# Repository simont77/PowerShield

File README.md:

# PowerShield
 This design is an extension board for any Raspberry Pi based astronomy tool, like Astroberry or StellarMate.
 The repository contains the electrical (ECAD) and mechanical (MCAD) design files.
 
# Electrical Design (ECAD)

## Features
* One power input
* 4pcs switchable (ON/OFF) not regulated outpus, each has maximum 3A load capability (CH1 ... CH4 - DC jack)
* 2pcs switchable (ON/OFF) or PWM controlled outputs, also with maximum 3A load capability for dew heaters (DEW1 and DEW2 - RCA)
* Fuse monitoring signals for each outputs, to detect fuse burn
* Integrated 5V/3A SMPS to power Raspberry Pi
* Integrated BME280 to measure, temperature, pressure and humidity
* Integrated GPS module with integrated antenna
* Connecting external GPS antenna
* Fan connector, supports 3,3V and 5V fans, fan can be switched ON/OFF.
* Input voltage monitoring, maximal range 20V
* Total output current monitoring, maximal range 16A, allowed total ouput curren is 15A
* Reverse polarity protection
* 4 pin 3,5mm jack to connect external sensors, or extension boards, communication interface can be selected with jumpers, I2C or one wire
* LED feedback for each outputs
* LED for GPS, e.g. show 3D fix (usage of this LED is SW dependent)

List of used ports and their funtions will be available in the Wiki section.

## What works
 Every features listed above are tested and working. Testing was done with terminal commands, like "gpio" or with testing scripts.

## What is not working
 Check the "Issues" section.

## What is needed
* INDI driver is on the way: https://github.com/rkaczorek/astroberry-powershield
* I am planning to perform thermal measurement, to see what is board thermal behaviour under maximal load condition.

# Mechanical Design (MCAD)
 Mechanical design was done based on Hammond Extruded Aluminum Enclosures design.

 The "extruded" part of the housing is prepared for 3D printing.
 The front and back plates are design in KiCAD as well and manufactured from 1,6mm thick PCB, the panelized gerber files are uploaded in the repository.

# Licence
 The licence is the CERN Open Hardware Licence version 2, and variant CERN-OHL-S
 Check the "LICENCE" file or original location of the licence:
 https://ohwr.org/cern_ohl_s_v2.txt
 
# Donation
If you like the design, think about to support me with a cup of coffee, a glas of beer...
This could help to develop further this design.

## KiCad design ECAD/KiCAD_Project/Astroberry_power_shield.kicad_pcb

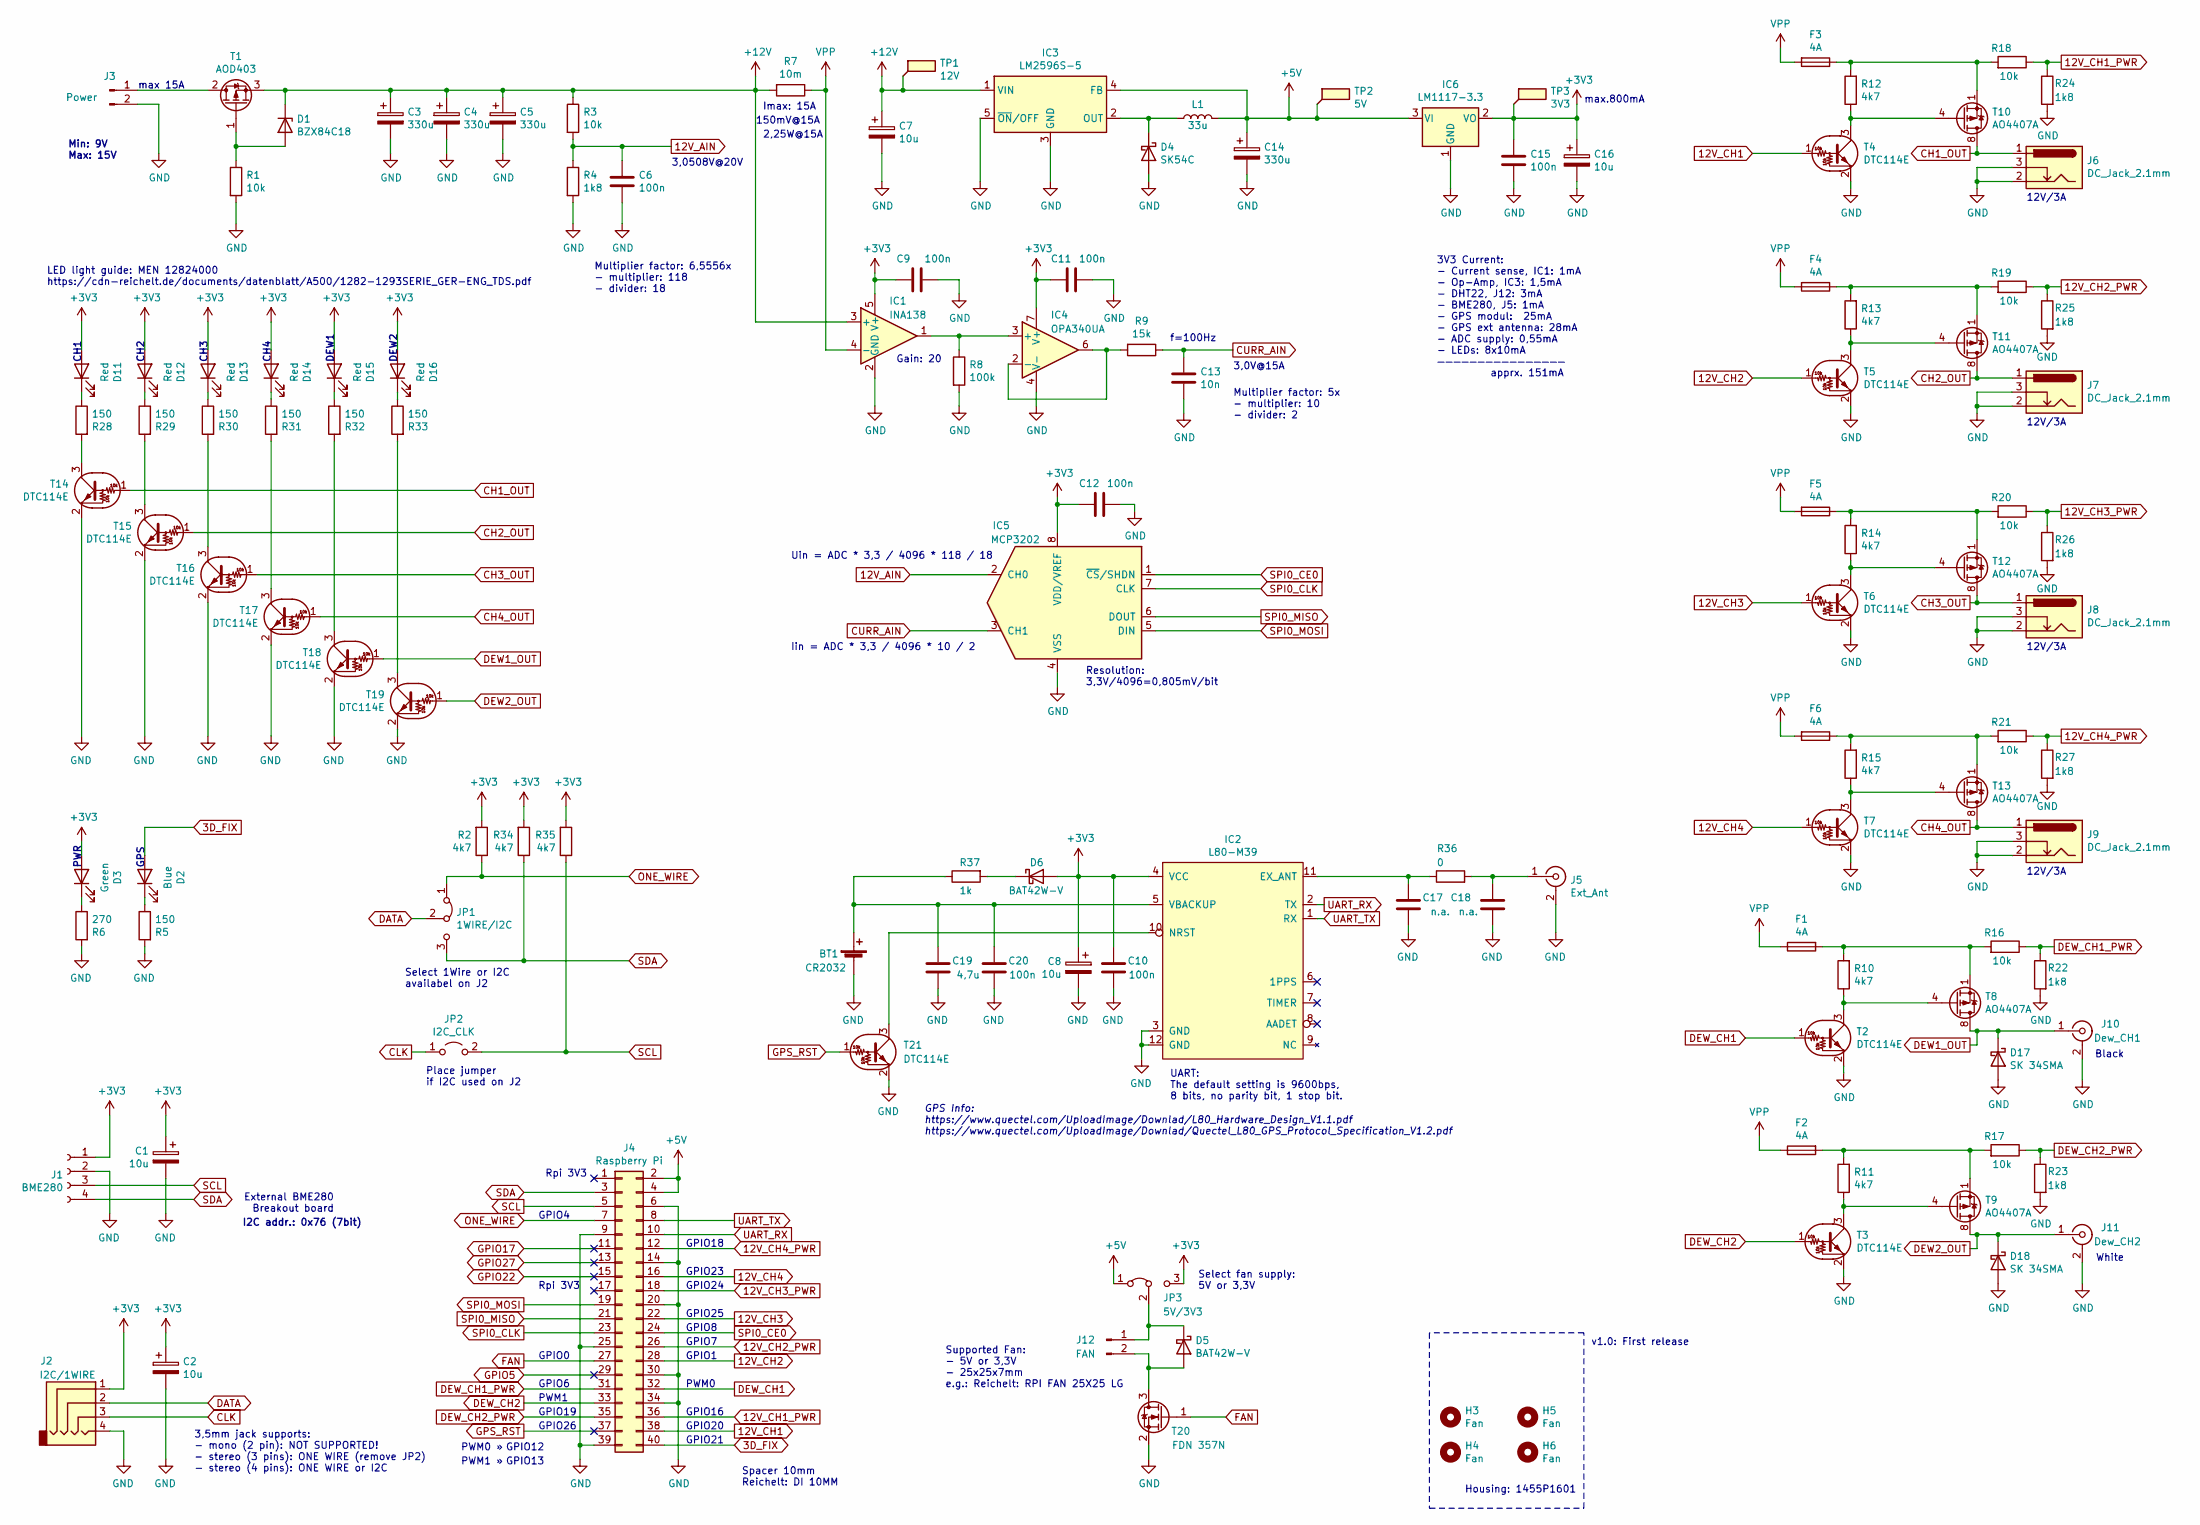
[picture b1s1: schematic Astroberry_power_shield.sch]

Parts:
BT1: CR2032; BatteryHolder_Keystone_3002_1x2032
C1, C2, C7, C8, C16: 10u; CP_EIA-6032-28_Kemet-C_Pad2.25x2.35mm_HandSolder
C3, C4, C5, C14: 330u; C_Elec_8x10.2; JLCPCB C286135
C6, C9, C10, C11, C12, C15, C20: 100n; C_0805_2012Metric; JLCPCB C49678
C13: 10n; C_0805_2012Metric; JLCPCB C1710
C17, C18: n.a.; C_0805_2012Metric
C19: 4,7u; C_0805_2012Metric; JLCPCB C1779
D1: BZX84C18; D_SOT-23_ANK; JLCPCB C35678
D2: Blue; LED_0805_2012Metric; JLCPCB C2293
D3: Green; LED_0805_2012Metric; JLCPCB C84257
D4: SK54C; D_SMC; JLCPCB C57579
D5, D6: BAT42W-V; D_SOD-123; JLCPCB C144923
D11, D12, D13, D14, D15, D16: Red; LED_0805_2012Metric; JLCPCB C84256
D17, D18: SK 34SMA; D_SMA; JLCPCB C65008
F1, F2, F3, F4, F5, F6: 4A; Litt_154_OMNI_BLOK
H3, H4, H5, H6: Fan; MountingHole_3.2mm_M3
IC1: INA138; SOT-23-5; JLCPCB C47914
IC2: L80-M39
IC3: LM2596S-5; TO-263-5_TabPin3; JLCPCB C10002
IC4: OPA340UA; SOIC-8_3.9x4.9mm_P1.27mm; JLCPCB C12247
IC5: MCP3202; SOIC-8_3.9x4.9mm_P1.27mm
IC6: LM1117-3.3; SOT-223; JLCPCB C126027
J1: BME280; BME280_holder
J2: I2C/1WIRE; LUM_1503_13
J3: Power; XT60PW-M20
J4: Raspberry Pi; Raspberry_pi_4_w_mounting_holes
J5: Ext_Ant; U.FL_Molex_MCRF_73412-0110_Vertical
J6, J7, J8, J9: DC_Jack_2.1mm; BKL_DC_Jack_2.1mm
J10: Dew_CH1; LUM_1553
J11: Dew_CH2; LUM_1553
J12: FAN; JST_PH_B2B-PH-K_1x02_P2.00mm_Vertical
JP1: 1WIRE/I2C; PinHeader_1x03_P2.54mm_Vertical
JP2: I2C_CLK; PinHeader_1x02_P2.54mm_Vertical
JP3: 5V/3V3; PinHeader_1x03_P2.54mm_Vertical
L1: 33u; L_12x12mm_H8mm; JLCPCB C169375
R1, R3, R16, R17, R18, R19, R20, R21: 10k; R_0805_2012Metric; JLCPCB C17414
R2, R10, R11, R12, R13, R14, R15, R34, R35: 4k7; R_0805_2012Metric; JLCPCB C17673
R4, R22, R23, R24, R25, R26, R27: 1k8; R_0805_2012Metric; JLCPCB C17398
R5, R28, R29, R30, R31, R32, R33: 150; R_0805_2012Metric; JLCPCB C17471
R6: 270; R_0805_2012Metric; JLCPCB C17590
R7: 10m; R_2512_6332Metric; JLCPCB C76242
R8: 100k; R_0805_2012Metric; JLCPCB C17407
R9: 15k; R_0805_2012Metric; JLCPCB C17475
R36: 0; R_0805_2012Metric; JLCPCB C17477
R37: 1k; R_0805_2012Metric; JLCPCB C17513
T1: AOD403; TO-252-2; JLCPCB C28969
T2, T3, T4, T5, T6, T7, T14, T15, T16, T17, T18, T19, T21: DTC114E; SOT-23; JLCPCB C14303
T8, T9, T10, T11, T12, T13: AO4407A; SOIC-8_3.9x4.9mm_P1.27mm; JLCPCB C16072
T20: FDN 357N; SOT-23
TP1: 12V; TestPoint_Pad_D2.0mm
TP2: 5V; TestPoint_Pad_D2.0mm
TP3: 3V3; TestPoint_Pad_D2.0mm

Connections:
3D_FIX: D2.2 (A), J4.40
12V_AIN: C6.1, IC5.2 (CH0), R3.2, R4.1
12V_CH1: J4.38, T4.1 (B)
12V_CH1_PWR: J4.36, R18.1, R24.1
12V_CH2: J4.28, T5.1 (B)
12V_CH2_PWR: J4.26, R19.1, R25.1
12V_CH3: J4.22, T6.1 (B)
12V_CH3_PWR: J4.18, R20.1, R26.1
12V_CH4: J4.16, T7.1 (B)
12V_CH4_PWR: J4.12, R21.1, R27.1
+3V3: C1.1, C2.1, C8.1, C9.2, C10.2, C11.2, C12.2, C15.1, C16.1, D3.2 (A), D6.2 (A), D11.2 (A), D12.2 (A), D13.2 (A), D14.2 (A), D15.2 (A), D16.2 (A), IC1.5 (V+), IC2.4 (VCC), IC4.7 (V+), IC5.8 (VDD/VREF), IC6.2 (VO), J1.1, J2.1, JP3.3 (B), R2.2, R34.2, R35.2, TP3.1
+5V: C14.1, IC3.4 (FB), IC6.3 (VI), J4.2, J4.4, JP3.1 (A), L1.2, TP2.1
+12V: C3.1, C4.1, C5.1, C7.1, D1.1 (K), IC1.3 (+), IC3.1 (VIN), R3.1, R7.2, T1.3 (S), TP1.1
CH1_OUT: J6.1, T10.5 (D), T10.6 (D), T10.7 (D), T10.8 (D), T14.1 (B)
CH2_OUT: J7.1, T11.5 (D), T11.6 (D), T11.7 (D), T11.8 (D), T15.1 (B)
CH3_OUT: J8.1, T12.5 (D), T12.6 (D), T12.7 (D), T12.8 (D), T16.1 (B)
CH4_OUT: J9.1, T13.5 (D), T13.6 (D), T13.7 (D), T13.8 (D), T17.1 (B)
CLK: J2.3, JP2.1 (A)
CURR_AIN: C13.1, IC5.3 (CH1), R9.1
DATA: J2.2, JP1.2 (C)
DEW1_OUT: D17.1 (K), J10.1 (In), T8.5 (D), T8.6 (D), T8.7 (D), T8.8 (D), T18.1 (B)
DEW2_OUT: D18.1 (K), J11.1 (In), T9.5 (D), T9.6 (D), T9.7 (D), T9.8 (D), T19.1 (B)
DEW_CH1: J4.32, T2.1 (B)
DEW_CH1_PWR: J4.31, R16.1, R22.1
DEW_CH2: J4.33, T3.1 (B)
DEW_CH2_PWR: J4.35, R17.1, R23.1
FAN: J4.27, T20.1 (G)
GND: BT1.2 (-), C1.2, C2.2, C3.2, C4.2, C5.2, C6.2, C7.2, C8.2, C9.1, C10.1, C11.1, C12.1, C13.2, C14.2, C15.2, C16.2, C17.1, C18.1, C19.1, C20.1, D4.2 (A), D17.2 (A), D18.2 (A), IC1.2 (GND), IC2.3 (GND), IC2.12 (GND), IC3.3 (GND), IC3.5 (~ON~/OFF), IC4.4 (V-), IC5.4 (VSS), IC6.1 (GND), J1.2, J2.4, J3.2, J4.6, J4.9, J4.14, J4.20, J4.25, J4.30, J4.34, J4.39, J5.2 (Ext), J6.2, J6.3, J7.2, J7.3, J8.2, J8.3, J9.2, J9.3, J10.2 (Ext), J11.2 (Ext), R1.2, R4.2, R5.2, R6.2, R8.2, R22.2, R23.2, R24.2, R25.2, R26.2, R27.2, T2.2 (E), T3.2 (E), T4.2 (E), T5.2 (E), T6.2 (E), T7.2 (E), T14.2 (E), T15.2 (E), T16.2 (E), T17.2 (E), T18.2 (E), T19.2 (E), T20.2 (S), T21.2 (E)
GPIO5: J4.29
GPIO17: J4.11
GPIO22: J4.15
GPIO27: J4.13
GPS_RST: J4.37, T21.1 (B)
unnamed: BT1.1 (+), C19.2, C20.2, IC2.5 (VBACKUP), R37.1
unnamed: C17.2, IC2.11 (EX_ANT), R36.1
unnamed: C18.2, J5.1 (In), R36.2
unnamed: D1.2 (A), R1.1, T1.1 (G)
unnamed: D2.1 (K), R5.1
unnamed: D3.1 (K), R6.1
unnamed: D4.1 (K), IC3.2 (OUT), L1.1
unnamed: D5.1 (K), J12.1, JP3.2 (C)
unnamed: D5.2 (A), J12.2, T20.3 (D)
unnamed: D6.1 (K), R37.2
unnamed: D11.1 (K), R28.1
unnamed: D12.1 (K), R29.1
unnamed: D13.1 (K), R30.1
unnamed: D14.1 (K), R31.1
unnamed: D15.1 (K), R32.1
unnamed: D16.1 (K), R33.1
unnamed: F1.2, R10.2, R16.2, T8.1 (S), T8.2 (S), T8.3 (S)
unnamed: F2.2, R11.2, R17.2, T9.1 (S), T9.2 (S), T9.3 (S)
unnamed: F3.1, R12.2, R18.2, T10.1 (S), T10.2 (S), T10.3 (S)
unnamed: F4.1, R13.2, R19.2, T11.1 (S), T11.2 (S), T11.3 (S)
unnamed: F5.1, R14.2, R20.2, T12.1 (S), T12.2 (S), T12.3 (S)
unnamed: F6.1, R15.2, R21.2, T13.1 (S), T13.2 (S), T13.3 (S)
unnamed: IC1.1, IC4.3 (+), R8.1
unnamed: IC2.10 (NRST), T21.3 (C)
unnamed: IC4.2 (-), IC4.6, R9.2
unnamed: J3.1, T1.2 (D)
unnamed: R10.1, T2.3 (C), T8.4 (G)
unnamed: R11.1, T3.3 (C), T9.4 (G)
unnamed: R12.1, T4.3 (C), T10.4 (G)
unnamed: R13.1, T5.3 (C), T11.4 (G)
unnamed: R14.1, T6.3 (C), T12.4 (G)
unnamed: R15.1, T7.3 (C), T13.4 (G)
unnamed: R28.2, T14.3 (C)
unnamed: R29.2, T15.3 (C)
unnamed: R30.2, T16.3 (C)
unnamed: R31.2, T17.3 (C)
unnamed: R32.2, T18.3 (C)
unnamed: R33.2, T19.3 (C)
ONE_WIRE: J4.7, JP1.1 (A), R2.1
SCL: J1.3, J4.5, JP2.2 (B), R35.1
SDA: J1.4, J4.3, JP1.3 (B), R34.1
SPI0_CE0: IC5.1 (~CS~/SHDN), J4.24
SPI0_CLK: IC5.7 (CLK), J4.23
SPI0_MISO: IC5.6 (DOUT), J4.21
SPI0_MOSI: IC5.5 (DIN), J4.19
UART_RX: IC2.2 (TX), J4.10
UART_TX: IC2.1 (RX), J4.8
VPP: F1.1, F2.1, F3.2, F4.2, F5.2, F6.2, IC1.4 (-), R7.1

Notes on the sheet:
3,0508V@20V
12V/3A
Imax: 15A
150mV@15A
Gain: 20
3,0V@15A
f=100Hz
White
Black
External BME280 Breakout board
Housing: 1455P1601
I2C addr.: 0x76 (7bit)
Min: 9V Max: 15V
3V3 Current: - Current sense, IC1: 1mA - Op-Amp, IC3: 1,5mA - DHT22, J12: 3mA - BME280, J5: 1mA - GPS modul: 25mA - GPS ext antenna: 28mA - ADC supply: 0,55mA - LEDs: 8x10mA ———————————————— apprx. 151mA
v1.0: First release
Rpi 3V3
max.800mA
2,25W@15A
PWM0
PWM1
GPIO18
GPIO23
GPIO24
GPIO25
GPIO8
GPIO7
GPIO1
GPIO16
GPIO20
GPIO4
GPIO19
GPIO6
LED light guide: MEN 12824000 https://cdn-reichelt.de/documents/datenblatt/A500/1282-1293SERIE_GER-ENG_TDS.pdf
PWR
CH1
CH2
CH3
CH4
DEW1
DEW2

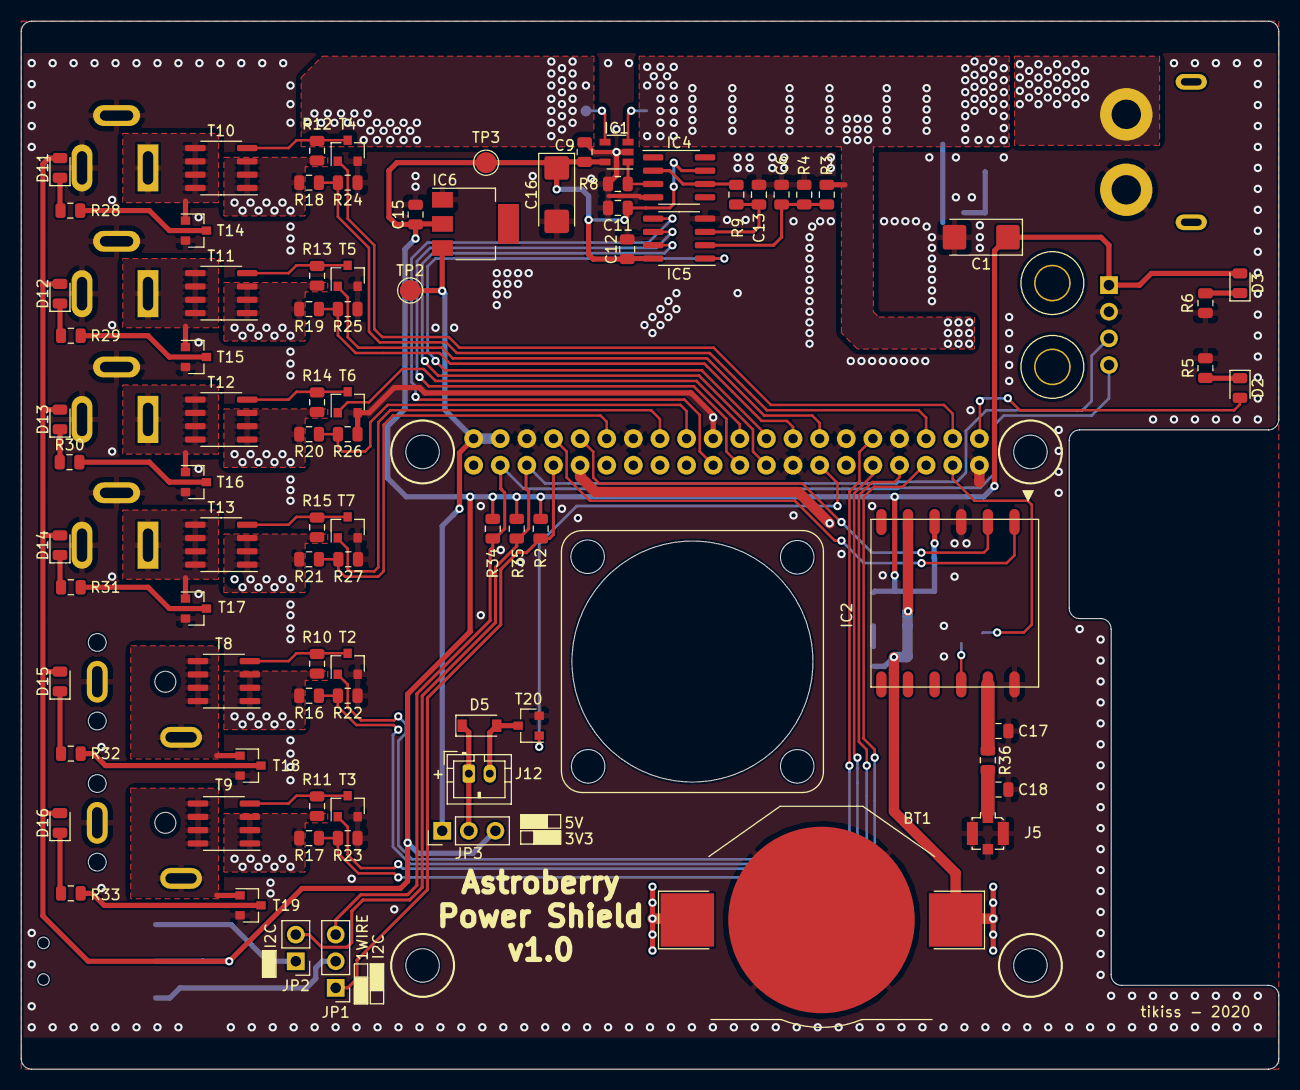
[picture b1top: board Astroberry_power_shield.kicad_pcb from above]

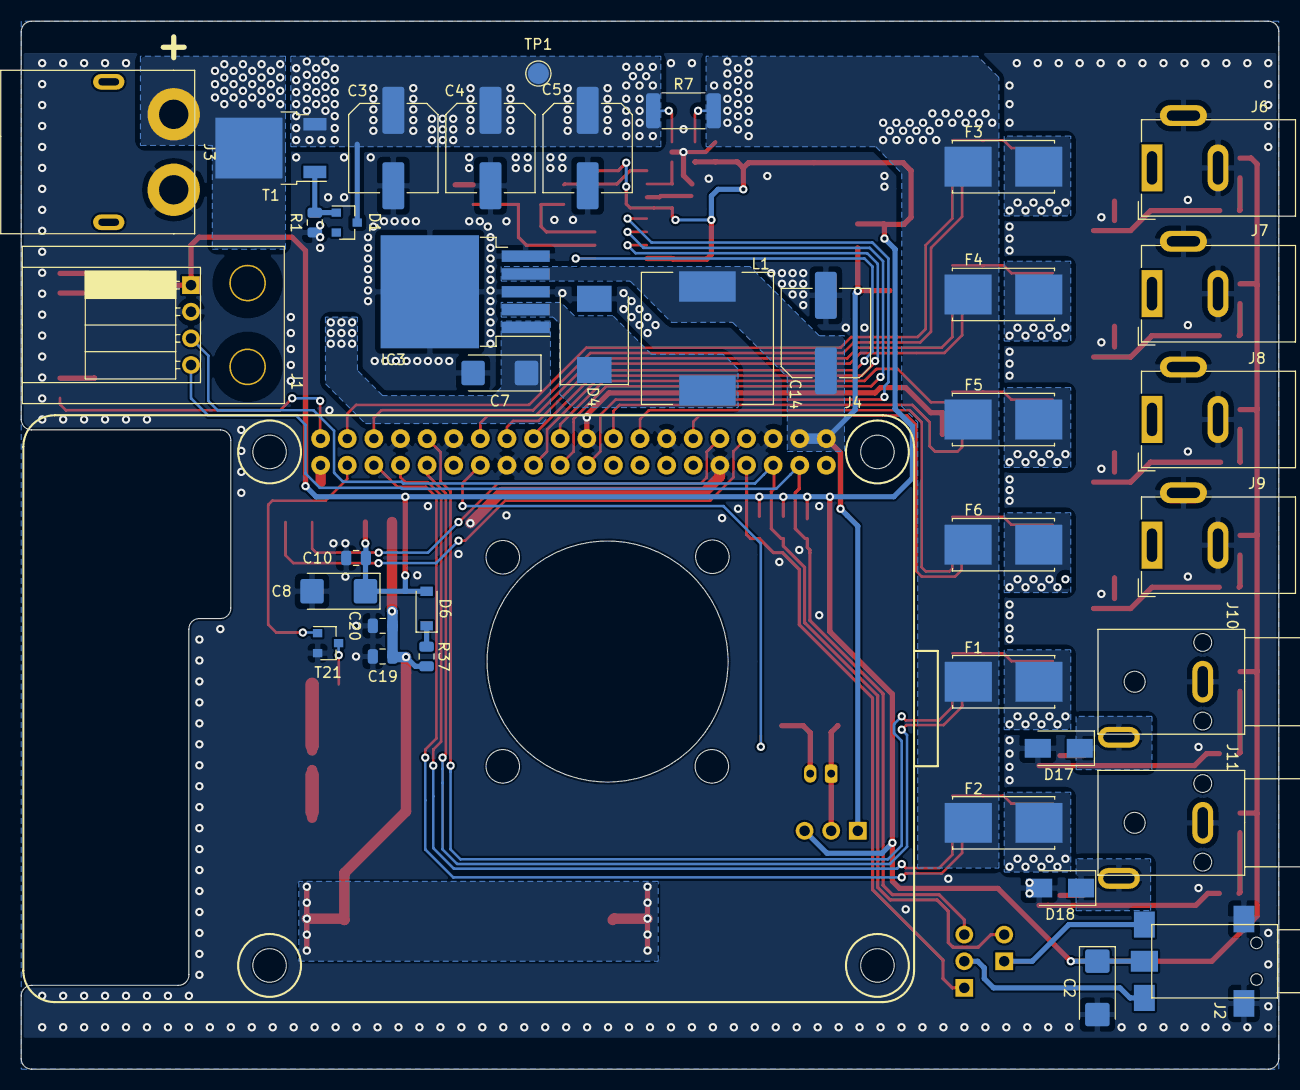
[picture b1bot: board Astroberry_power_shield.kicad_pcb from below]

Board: 2 copper layers, 120.0 x 100.0 mm, 128 parts (38 on the bottom side), 77 nets.

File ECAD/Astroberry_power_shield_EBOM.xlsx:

Designer | Tibor Kiss
Source: | Astroberry Power Shield v1.0
Date: | 2020 September 26, Saturday 18:41:44
Tool: | Eeschema (5.1.6-0-10_14)
Generator: | bom_csv_grouped_by_value.py
Component Count: | 125
Item | Qty | Reference(s) | Value | LibPart | Footprint | Reichelt
1 | 1 | BT1 | CR2032 | Device:Battery_Cell | Battery:BatteryHolder_Keystone_3002_1x2032 | -
2 | 5 | C1, C2, C7, C8, C16 | 10u | Device:CP | Capacitor_Tantalum_SMD:CP_EIA-6032-28_Kemet-C_Pad2.25x2.35mm_HandSolder | T491C 10U 25
3 | 4 | C3, C4, C5, C14 | 330u | Device:CP | Capacitor_SMD:C_Elec_8x10.2 | VF 330/25 K-F
4 | 7 | C6, C9, C10, C11, C12, C15, C20 | 100n | Device:C | Capacitor_SMD:C_0805_2012Metric | KEM X7R0805 100N
5 | 1 | C13 | 10n | Device:C | Capacitor_SMD:C_0805_2012Metric | KEM X7R0805 10N
6 | 2 | C17, C18 | n.a. | Device:C | Capacitor_SMD:C_0805_2012Metric | -
7 | 1 | C19 | 4,7u | Device:C | Capacitor_SMD:C_0805_2012Metric
8 | 1 | D1 | BZX84C18 | Diode:BZX84Cxx | Diode_SMD:D_SOT-23_ANK | BZX 84-C18 NXP
9 | 1 | D2 | Blue | Device:LED | LED_SMD:LED_0805_2012Metric
10 | 1 | D3 | Green | Device:LED | LED_SMD:LED_0805_2012Metric | SMD-LED 0805 GN
11 | 1 | D4 | SK54C | Diode:B320 | Diode_SMD:D_SMC | SK 54C
12 | 2 | D5, D6 | BAT42W-V | Diode:BAT42W-V | Diode_SMD:D_SOD-123 | BAT 42W
13 | 6 | D11, D12, D13, D14, D15, D16 | Red | Device:LED | LED_SMD:LED_0805_2012Metric | SMD-LED 0805 RT
14 | 2 | D17, D18 | SK 34SMA | Device:D_Schottky | Diode_SMD:D_SMA | SK 34SMA DIO
15 | 6 | F1, F2, F3, F4, F5, F6 | 4A | Device:Fuse | MyFuses:Litt_154_OMNI_BLOK | SMD-HASF 4,0A
16 | 4 | H3, H4, H5, H6 | Fan | Mechanical:MountingHole | MountingHole:MountingHole_3.2mm_M3 | -
17 | 1 | IC1 | INA138 | Amplifier_Current:INA138 | Package_TO_SOT_SMD:SOT-23-5 | INA 138 NA/250
18 | 1 | IC2 | L80-M39 | MyGPS:L80-M39 | MyGPS:L80-M39
19 | 1 | IC3 | LM2596S-5 | Regulator_Switching:LM2596S-5 | Package_TO_SOT_SMD:TO-263-5_TabPin3 | LM 2596 S-5.0
20 | 1 | IC4 | OPA340UA | Amplifier_Operational:OPA340UA | Package_SO:SOIC-8_3.9x4.9mm_P1.27mm | OPA 340 UA
21 | 1 | IC5 | MCP3202 | Analog_ADC:MCP3202 | Package_SO:SOIC-8_3.9x4.9mm_P1.27mm | MCP3202-CI/SN
22 | 1 | IC6 | LM1117-3.3 | Regulator_Linear:LM1117-3.3 | Package_TO_SOT_SMD:SOT-223 | TS 1117 BCW33
23 | 1 | J1 | BME280 | Connector:Conn_01x04_Female | MyMechanic:BME280_holder
24 | 1 | J2 | I2C/1WIRE | MyConnectors:AudioJack_4pin | MyConnectors:LUM_1503_13 | LUM 1503-13V
25 | 1 | J3 | Power | Connector:Conn_01x02_Male | MyConnectors:XT60PW-M20 | -
26 | 1 | J4 | Raspberry Pi | Connector_Generic:Conn_02x20_Odd_Even | MyRaspberry:Raspberry_pi_4_w_mounting_holes | MPE 094-2-040
27 | 1 | J5 | Ext_Ant | Connector:Conn_Coaxial | Connector_Coaxial:U.FL_Molex_MCRF_73412-0110_Vertical
28 | 4 | J6, J7, J8, J9 | DC_Jack_2.1mm | MyConnectors:DC_Jack_2.1mm | MyConnectors:BKL_DC_Jack_2.1mm | DC BU21 90
29 | 1 | J10 | Dew_CH1 | Connector:Conn_Coaxial | MyConnectors:LUM_1553 | LUM 1553 02 SW
30 | 1 | J11 | Dew_CH2 | Connector:Conn_Coaxial | MyConnectors:LUM_1553 | LUM 1553 02 WS
31 | 1 | J12 | FAN | Connector:Conn_01x02_Male | Connector_JST:JST_PH_B2B-PH-K_1x02_P2.00mm_Vertical
32 | 1 | JP1 | 1WIRE/I2C | Jumper:Jumper_3_Bridged12 | Connector_PinHeader_2.54mm:PinHeader_1x03_P2.54mm_Vertical
33 | 1 | JP2 | I2C_CLK | Jumper:Jumper_2_Open | Connector_PinHeader_2.54mm:PinHeader_1x02_P2.54mm_Vertical
34 | 1 | JP3 | 5V/3V3 | Jumper:Jumper_3_Bridged12 | Connector_PinHeader_2.54mm:PinHeader_1x03_P2.54mm_Vertical
35 | 1 | L1 | 33u | Device:L | Inductor_SMD:L_12x12mm_H8mm | L-PIS4728 33¬µ
36 | 8 | R1, R3, R16, R17, R18, R19, R20, R21 | 10k | Device:R | Resistor_SMD:R_0805_2012Metric | RND 0805 1 10K
37 | 9 | R2, R10, R11, R12, R13, R14, R15, R34, R35 | 4k7 | Device:R | Resistor_SMD:R_0805_2012Metric | RND 0805 1 4,7K
38 | 7 | R4, R22, R23, R24, R25, R26, R27 | 1k8 | Device:R | Resistor_SMD:R_0805_2012Metric | RND 0805 1 1,8K
39 | 7 | R5, R28, R29, R30, R31, R32, R33 | 150 | Device:R | Resistor_SMD:R_0805_2012Metric | RND 0805 1 150
40 | 1 | R6 | 270 | Device:R | Resistor_SMD:R_0805_2012Metric | RND 0805 1 270
41 | 1 | R7 | 10m | Device:R | Resistor_SMD:R_2512_6332Metric | ISA SMT-R010-1
42 | 1 | R8 | 100k | Device:R | Resistor_SMD:R_0805_2012Metric | RND 0805 1 100K
43 | 1 | R9 | 15k | Device:R | Resistor_SMD:R_0805_2012Metric | RND 0805 1 15K
44 | 1 | R36 | 0 | Device:R | Resistor_SMD:R_0805_2012Metric
45 | 1 | R37 | 1k | Device:R | Resistor_SMD:R_0805_2012Metric | RND 0805 1 1K
46 | 1 | T1 | AOD403 | Transistor_FET:SUD19P06-60 | Package_TO_SOT_SMD:TO-252-2 | AO D403
47 | 13 | T2, T3, T4, T5, T6, T7, T14, T15, T16, T17, T18, T19, T21 | DTC114E | Transistor_BJT:DTC114E | Package_TO_SOT_SMD:SOT-23 | PDTC 114ET NXP
48 | 6 | T8, T9, T10, T11, T12, T13 | AO4407A | Transistor_FET:IRF7404 | Package_SO:SOIC-8_3.9x4.9mm_P1.27mm | AO 4407A
49 | 1 | T20 | FDN 357N | Transistor_FET:ZXMN3A01F | Package_TO_SOT_SMD:SOT-23 | FDN 357N

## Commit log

2020-09-25 First release
    First release upload to GitHub
2020-09-26 Updated README.md
    Main description of the design is added.
2020-09-26 EBOM created
    EBOM for v1.0 is ready
2020-10-06 Update README.md
    INDI driver is on the way
